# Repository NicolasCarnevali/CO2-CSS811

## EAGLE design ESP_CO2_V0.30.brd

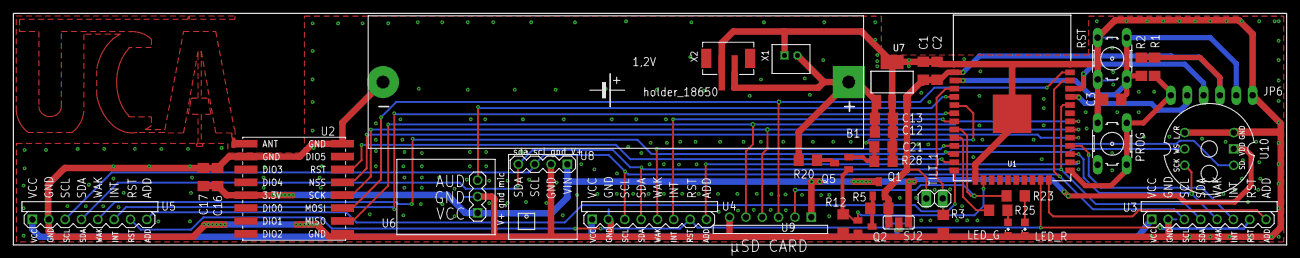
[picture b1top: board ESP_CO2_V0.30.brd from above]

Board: 2 copper layers, 197.9 x 36.0 mm, 40 parts (1 on the bottom side), 36 nets.

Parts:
B1: 18650_HOLDER; 18650
C1, C3, C13, C17: 100n; C1206
C2, C12: 10u; C1206
C16: 4.7u; C1206
C21: 10n; C1206
JP6: 1X06/90
LED_G: SML0805
LED_R: SML0805
PROG: B3F-10XX
Q1: SI2305CDS; SOT23
Q2: BSS131; SOT23
Q5: BSS138; SOT23
R1, R3: 100k; R1206
R2, R28: 10k; R1206
R5, R12: 33k; R1206
R20: 27k; R1206
R23: 150; R1206
R25: 100; R1206
RST: B3F-10XX
SJ2: SJ_2
TILT_1: 1X02
U1: ESP-WROOM-03
U2: WIRELESS-LORA-RFM95W#SMD
U3, U4, U5: CCS811; CO2_V
U6: SON
U7: MIC5239S; SOT223
U8: TEMP-HUM-PRES-BME280H; TEMP-HUM-PRES-BME280-H
U9: CARD-µSD-ADAPTERMINI; CARD-MINI--µSD-READER
U10: SOUND-DETECTOR-INMP441
X1: B2B-PH-K-S
X2: B2B-PH-SM4-TB

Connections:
+UB: B1.+, C12.1, C13.1, R20.2, U7.1, X1.2, X2.2
ADD1: U1.24, U3.ADD
ADD2: U1.26, U4.ADD
ADD3: U1.14, U5.ADD
GND: B1.-, C1.2, C2.2, C3.2, C12.2, C13.2, C16.2, C17.2, C21.2, JP6.1, LED_G.C, LED_R.C, PROG.3, PROG.4, Q2.2, R3.2, R12.2, R28.2, RST.3, RST.4, U1.1, U1.15, U1.38, U1.GND, U2.A1, U2.A8, U2.B7, U3.GND, U4.GND, U5.GND, U6.GND, U7.2, U7.4, U8.2, U9.GND, U10.GND, U10.L/R, X1.1, X2.1
INT1: U1.28, U3.INT
INT2: U1.8, U4.INT
INT3: U1.7, U5.INT
IO0: JP6.6, PROG.1, PROG.2, R1.2, U1.25
LED_G: R25.1, U1.10
LED_R: R23.1, U1.9, U9.CS
MEASURE: Q2.1, Q5.1, R12.1, U1.16
MIC: U1.5, U6.AUD
MISO: U1.31, U2.A2, U9.MISO
MOSI: U1.37, U2.A3, U9.MOSI
unnamed: Q1.1, Q2.3, R5.1
unnamed: Q5.3, R20.1
unnamed: LED_R.A, R23.2
unnamed: LED_G.A, R25.2
RFM_NSS: U1.29, U2.A5
RFM_RST: U1.13, U2.A6
RFM_SCK: U1.30, U2.A4, U9.SCK
RST: C3.1, JP6.2, R2.1, RST.1, RST.2, U1.3
RST_CO2: U1.23, U3.RST, U4.RST, U5.RST
RX: JP6.5, U1.34
SCL: U1.36, U3.SCL, U4.SCL, U5.SCL, U8.3
SDA: U1.33, U3.SDA, U4.SDA, U5.SDA, U8.4
TILT1: R3.1, TILT_1.1, U1.4
TX: JP6.4, U1.35
V+: C16.1, C17.1, Q1.3, SJ2.1, U2.B4, U6.VCC, U8.1, U9.VCC, U10.VDD
V+CO2: SJ2.2, U3.VCC, U4.VCC, U5.VCC
VBAT: C21.1, Q5.2, R28.1, U1.6
VCC: C1.1, C2.1, JP6.3, Q1.2, R1.1, R2.2, R5.2, SJ2.3, TILT_1.2, U1.2, U7.3
WAK1: U1.27, U3.WAK, U10.SCK
WAK2: U1.11, U4.WAK, U10.SD
WAK3: U1.12, U5.WAK, U10.WS

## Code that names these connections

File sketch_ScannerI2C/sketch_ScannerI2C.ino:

#include <Wire.h>
#define MEASURE 13
#define RST_CO2 150
#define WAK_PIN1 16
#define WAK_PIN2 26
#define WAK_PIN3 27
#define SDA 21
#define SCL 22
#define ADD1 15
#define ADD2 12
#define ADD3 4
#define INT3 17
void setup() {
  Wire.begin();
  pinMode(ADD1,OUTPUT);
  pinMode(ADD2,OUTPUT);
  pinMode(ADD3,OUTPUT);
  pinMode(INT3,INPUT);
  pinMode(MEASURE,OUTPUT);
  pinMode(RST_CO2,OUTPUT);
  pinMode(WAK_PIN1,OUTPUT);
  pinMode(WAK_PIN2,OUTPUT);
  pinMode(WAK_PIN3,OUTPUT);
  Serial.begin(115200);
  Serial.println("\nI2C Scanner");
  digitalWrite(MEASURE, HIGH);
  digitalWrite(WAK_PIN1, LOW);
  digitalWrite(WAK_PIN2, HIGH);
  digitalWrite(WAK_PIN3, HIGH);
 //digitalWrite(INT3,HIGH);
  digitalWrite(RST_CO2, LOW);
  delay(100);
  //digitalWrite(RST_CO2, HIGH);
  digitalWrite(ADD1,LOW);
  digitalWrite(ADD3,HIGH);
  Wire.begin(SDA, SCL);
  Wire.setClock(1000);
}
 
void loop() {
  byte error, address;
  int nDevices;
  
  Serial.println("Scanning...");
  nDevices = 0;
  for(address = 1; address < 127; address++ ) {
     //Serial.println("1");
    Wire.beginTransmission(address);
    //Serial.println("2");
    error = Wire.endTransmission();
    //Serial.println("3");
    if (error == 0) {
      Serial.print("I2C device found at address 0x");
      if (address<16) {
        Serial.print("0");
      }
      Serial.println(address,HEX);
      nDevices++;
    }
    else if (error==4) {
      Serial.print("Unknow error at address 0x");
      if (address<16) {
        Serial.print("0");
      }
      Serial.println(address,HEX);
    }    
  }
  if (nDevices == 0) {
    Serial.println("No I2C devices found\n");
  }
  else {
    Serial.println("done\n");
  }
  delay(5000);          
}

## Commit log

2023-11-01 Create CSS811.docx
    Rapport d'avancement du projet
2023-11-06 sche
2023-12-03 Rapports Elyes des séances
    Les rapports de Elyes des séances du 6/11/2023 et du 20/11/2023
2023-12-04 Sketch
2023-12-04 last update
2023-12-04 Table des pins de l'esp 32
2023-12-04 Sketch Arduino
    1-NEW sketch to measure the temperature and humidity
    2- Update the I2C scanner to get the address of the sensor
2023-12-04 Create readCO2.ino
    New sketch to measure CO2
2023-12-04 MERCI
2023-12-04 Create Rapport_ElyesZantour_4122023.docx
    Rapport Elyes de la séance du 4-12-2023
2024-02-13 Modification seance du 04/12 et 22/12
    Ajouter le sketch de mesure du CO2, adapter le code du I2C scanner, rajouter les rapports des deux séances et modifier le schématique de la carte sur eagle
2024-02-16 Seance du 16/02/2024
    J'ai reussi a faire fonctioner les 3 capteurs sur la carte dev ESP32, carte grille, nouveau schematique
2024-05-16 Add files via upload
    Rapport_technique_projet_Electronique.pdf
2025-03-25 File
2025-04-27 All sketch
2025-05-19 Memoire

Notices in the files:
parts and their libraries:
diy-modules: Released under the Creative Commons Attribution 4.0 International License: http://creativecommons.org/licenses/by/4.0
micrel: Copyright (C) 2008, Bob Starr
